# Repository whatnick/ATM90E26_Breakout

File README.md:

# ATM90E26_Breakout
Breakout Board for ATMEL ATM90E26 single phase energy monitor.

If you would like to build one yourself and send me some credits towards new PCB's please order this board via PCBs.io below:

<a href="https://PCBs.io/share/8nvma"></img></a>

You can also order fully assembled and tested boards directly from me via Tindie:
https://www.tindie.com/products/whatnick/atm90e26-breakout/

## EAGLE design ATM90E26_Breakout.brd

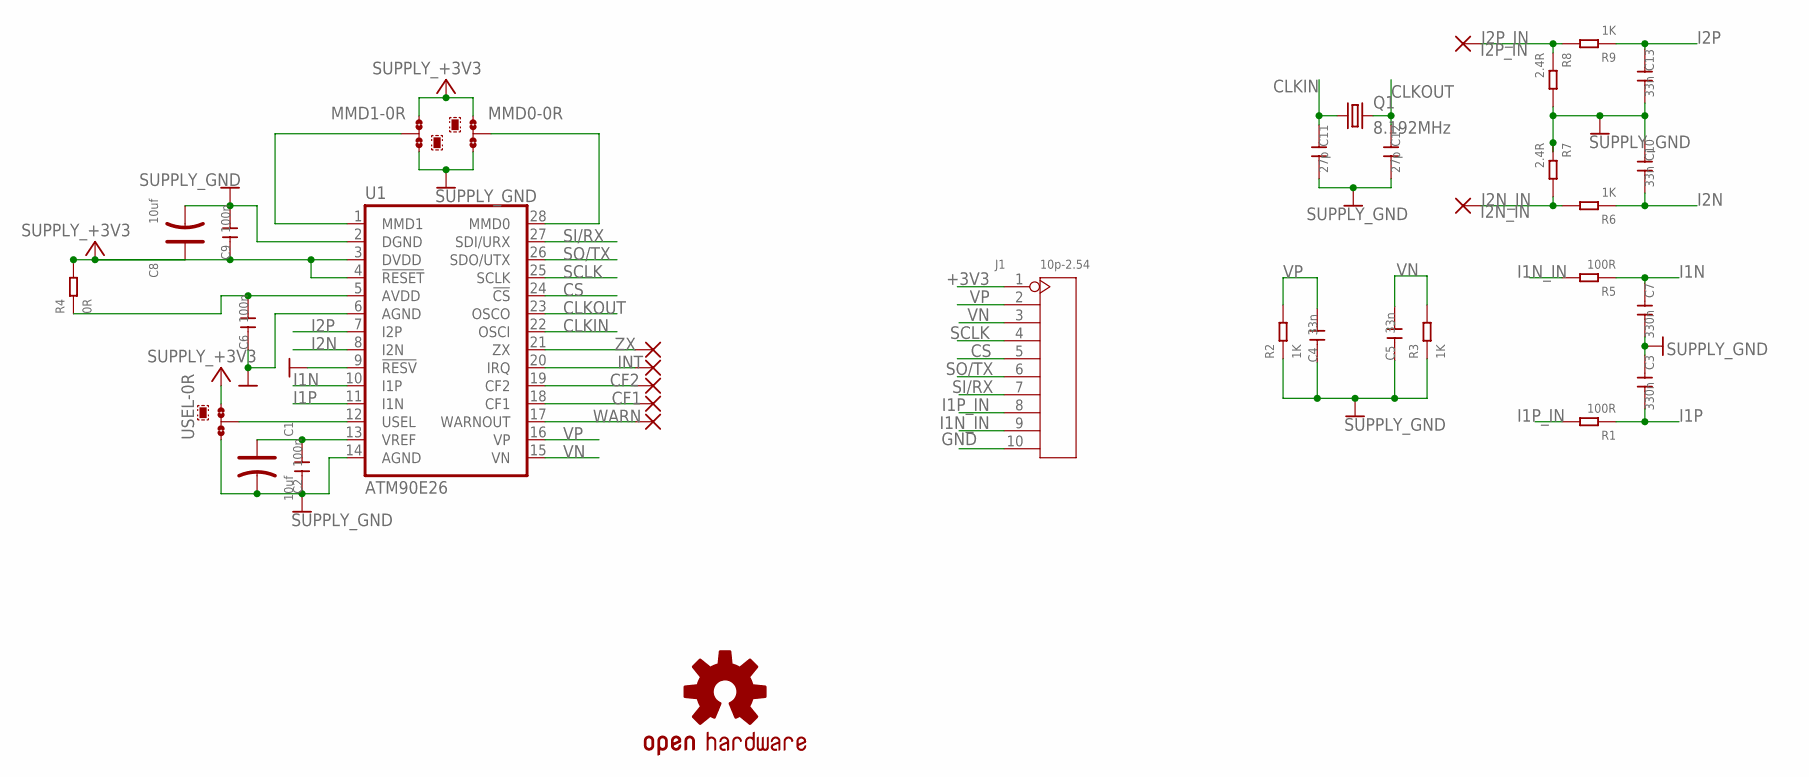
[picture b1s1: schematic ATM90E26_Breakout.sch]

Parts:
C1, C8: 10uf; AVX-A
C2, C6, C9: 100n; C0603
C3, C7: 330n; C0603
C4, C5, C10, C13: 33n; C0603
C11, C12: 27p; C0603
CF1, CF2: WIREPADSMD1,27-254; SMD1,27-2,54
I2N_IN, I2P_IN: WIREPADSMD1,27-254; SMD1,27-2,54
INT: WIREPADSMD1,27-254; SMD1,27-2,54
J1: 10p-2.54; H10-2.54
LOGO1: OSHW-LOGOM; OSHW-LOGO-M
MMD0, MMD1: 0R-JUMPA; A0R-JMP
Q1: 8.192MHz; HC49UP
R1, R5: 100R; R0603
R2, R3, R6, R9: 1K; R0603
R4: 0R; R0603
R7, R8: 2.4R; R0603
U1: ATM90E26; SSOP-28
USEL: 0R-JUMPA; A0R-JMP
WARN: WIREPADSMD1,27-254; SMD1,27-2,54
ZX: WIREPADSMD1,27-254; SMD1,27-2,54

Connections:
+3V3: C8.+, C9.1, J1.1, MMD0.1, MMD1.3, R4.2, U1.3 (DVDD), U1.4 (!RESET), USEL.1
CLKIN: C11.1, Q1.1, U1.22 (OSCI)
CLKOUT: C12.1, Q1.2, U1.23 (OSCO)
CS: J1.5, U1.24 (!CS)
GND: C1.-, C2.1, C3.1, C4.1, C5.1, C6.1, C7.2, C8.-, C9.2, C10.1, C11.2, C12.2, C13.2, J1.10, MMD0.3, MMD1.1, R2.1, R3.1, R7.1, R8.2, U1.2 (DGND), U1.6 (AGND), U1.9 (!RESV), U1.14 (AGND), USEL.3
I1N: C7.1, R5.1, U1.10 (I1P)
I1N_IN: J1.9, R5.2
I1P: C3.2, R1.1, U1.11 (I1N)
I1P_IN: J1.8, R1.2
I2N: C10.2, R6.1, U1.8 (I2N)
I2N_IN: I2N_IN.1, R6.2, R7.2
I2P: C13.1, R9.1, U1.7 (I2P)
I2P_IN: I2P_IN.1, R8.1, R9.2
unnamed: MMD1.2, U1.1 (MMD1)
unnamed: MMD0.2, U1.28 (MMD0)
unnamed: C6.2, R4.1, U1.5 (AVDD)
unnamed: CF1.1, U1.18 (CF1)
unnamed: CF2.1, U1.19 (CF2)
unnamed: U1.12 (USEL), USEL.2
unnamed: U1.21 (ZX), ZX.1
unnamed: INT.1, U1.20 (IRQ)
unnamed: U1.17 (WARNOUT), WARN.1
SCLK: J1.4, U1.25 (SCLK)
SI/RX: J1.7, U1.27 (SDI/URX)
SO/TX: J1.6, U1.26 (SDO/UTX)
VN: C5.2, J1.3, R3.2, U1.15 (VN)
VP: C4.2, J1.2, R2.2, U1.16 (VP)
VREF: C1.+, C2.2, U1.13 (VREF)

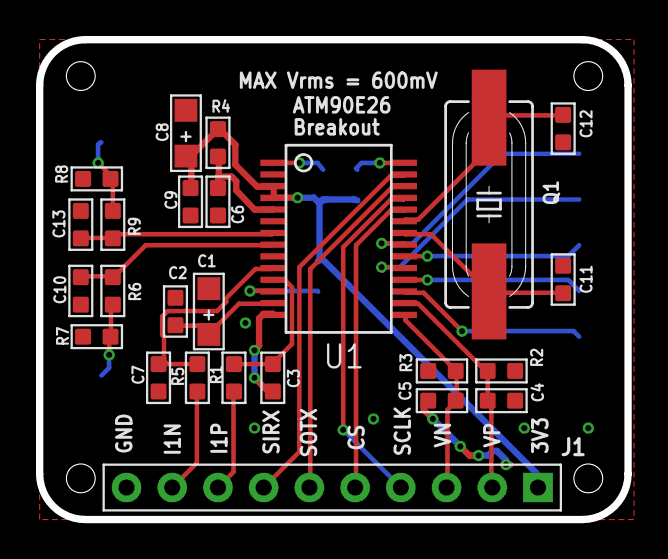
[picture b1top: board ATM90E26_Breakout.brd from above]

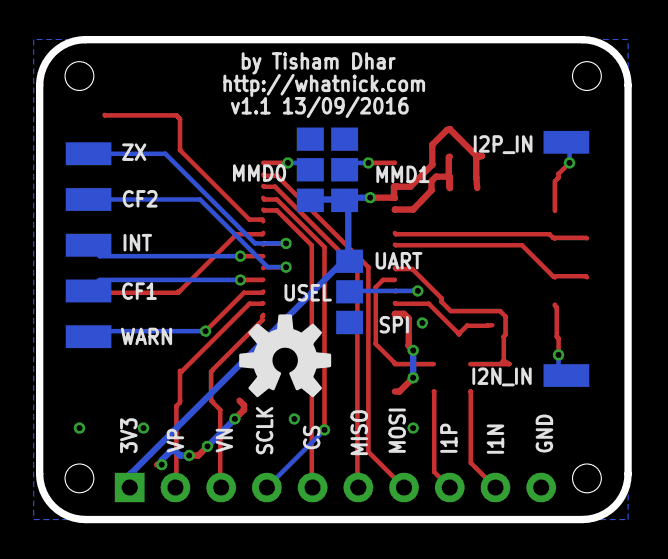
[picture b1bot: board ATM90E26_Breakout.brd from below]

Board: 2 copper layers, 32.7 x 26.7 mm, 36 parts (11 on the bottom side), 28 nets.

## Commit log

2016-04-03 Initial import
2016-04-04 Cosmetic changes to v1.0 ready for first fab
2016-09-12 Added labels for comm mode jumpers
2016-11-16 Hackvana DRU
2016-11-17 Created README
2018-02-03 Added documentation images

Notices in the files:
parts and their libraries:
SparkFun-Aesthetics: Licensing: Creative Commons ShareAlike 4.0 International - https://creativecommons.org/licenses/by-sa/4.0
